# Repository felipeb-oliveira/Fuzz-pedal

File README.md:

# Fuzz-pedal
A Fuzz guitar effect pedal, designed with inspiration for some classic Fuzz pedals.

## About
This guitar pedal was designed by me, and inspired by classic and simple Fuzz pedals. This was the second guitar pedal I ever projected, so there's definetely room for improvement. I used common two emmiter transistor configurations, with a DC bias which is later cut out by capacitors. The first transistor is responsible for most of the wave clipping, and the second one was designed so it would finish shaping the wave and adjusting the gain. There are two potentiometers, one for the Fuzz control, and one for the overall volume.

## Fuzz Schematic
*This is only the fuzz distortion circuit, without the inputs, outputs and supply circuits. Please open the 'Fuzz.sch' file for the full circuit.*

## Board

## Results
The results were as expected: hard wave clipping with high assymetry, as seen below.

Low Fuzz:

High Fuzz:

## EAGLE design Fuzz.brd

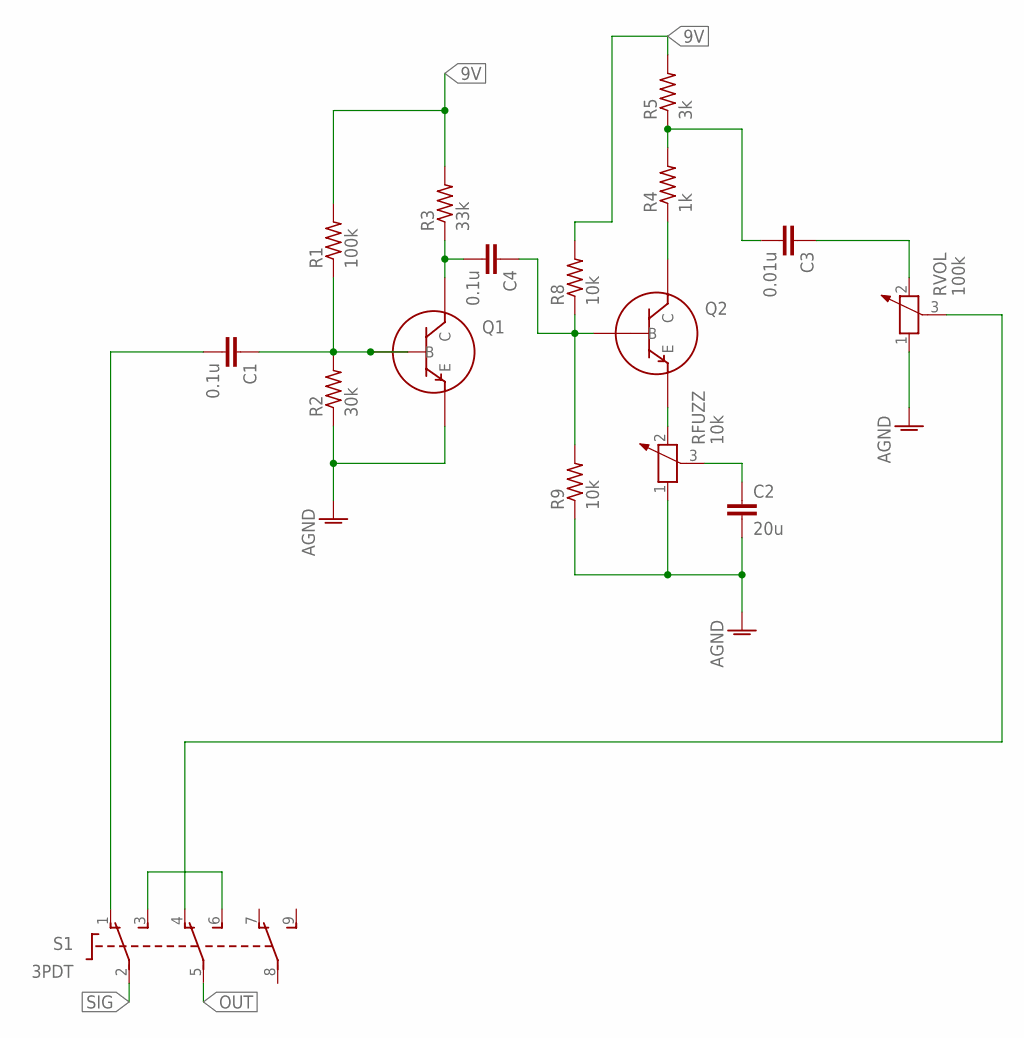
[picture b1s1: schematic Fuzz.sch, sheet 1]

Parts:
C1, C4: 0.1u; C025-024X044
C2: 20u; C025-024X044
C3: 0.01u; C025-024X044
R1: 100k; 0204V
R2: 30k; 0204V
R3: 33k; 0204V
R4: 1k; 0204V
R5: 3k; 0204V
R8, R9: 10k; 0204V
RFUZZ: 10k; PT-10
RVOL: 100k; PT-10
S1: 3PDT

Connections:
9V: R1.2, R3.2, R5.2, R8.2; also elsewhere on the board
AGND: C2.2, R2.1, R9.1, RFUZZ.1, RVOL.1; also elsewhere on the board
FIN: C1.1, R1.1, R2.2; also elsewhere on the board
FULL: R4.1; also elsewhere on the board
INT: C4.1, R8.1, R9.2; also elsewhere on the board
INTRAW: C4.2, R3.1; also elsewhere on the board
unnamed 6: RFUZZ.2; also elsewhere on the board
unnamed: S1.3 (S1), S1.6 (S2)
unnamed: C1.2, S1.1 (O1)
unnamed: C3.1, RVOL.2
unnamed: C2.1, RFUZZ.3
OUT: RVOL.3, S1.4 (O2), S1.5 (P2); also elsewhere on the board
RAW: C3.2, R4.2, R5.1
SIG: S1.2 (P1); also elsewhere on the board

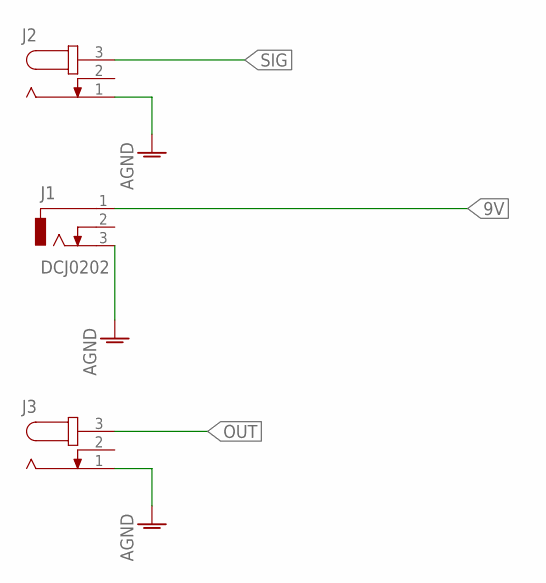
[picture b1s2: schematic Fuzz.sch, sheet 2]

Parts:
J1: DCJ0202
J2, J3: JACK-PLUG1; SPC4078

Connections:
9V: J1.1; also elsewhere on the board
AGND: J1.3, J2.1, J3.1; also elsewhere on the board
OUT: J3.3; also elsewhere on the board
SIG: J2.3; also elsewhere on the board

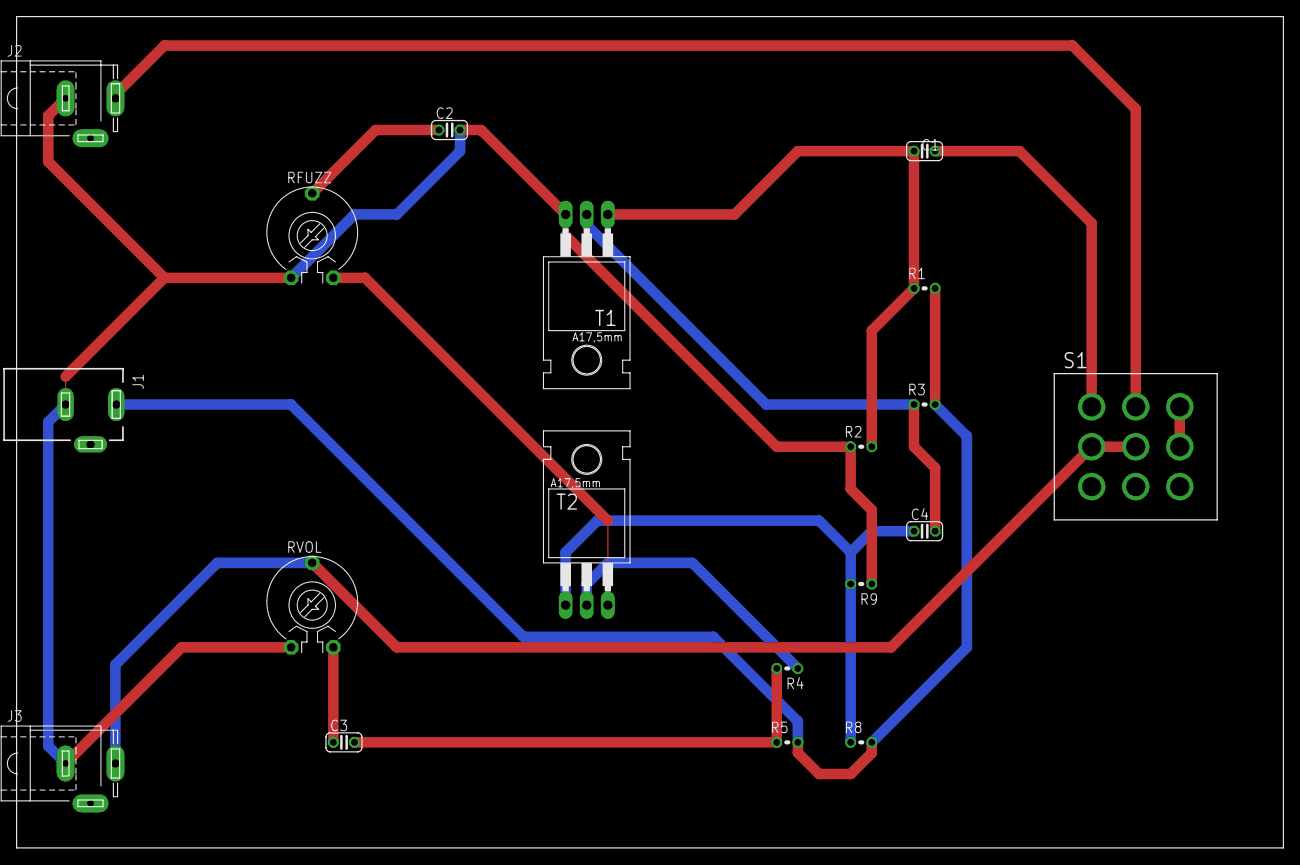
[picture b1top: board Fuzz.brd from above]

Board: 2 copper layers, 152.4 x 100.0 mm, 19 parts (0 on the bottom side), 14 nets.

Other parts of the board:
T1, T2: 2SC2509H; TO220

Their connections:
AGND: T1.3; also elsewhere on the board
FIN: T1.1; also elsewhere on the board
FULL: T2.2; also elsewhere on the board
INT: T2.1; also elsewhere on the board
INTRAW: T1.2; also elsewhere on the board
unnamed 6: T2.3; also elsewhere on the board
